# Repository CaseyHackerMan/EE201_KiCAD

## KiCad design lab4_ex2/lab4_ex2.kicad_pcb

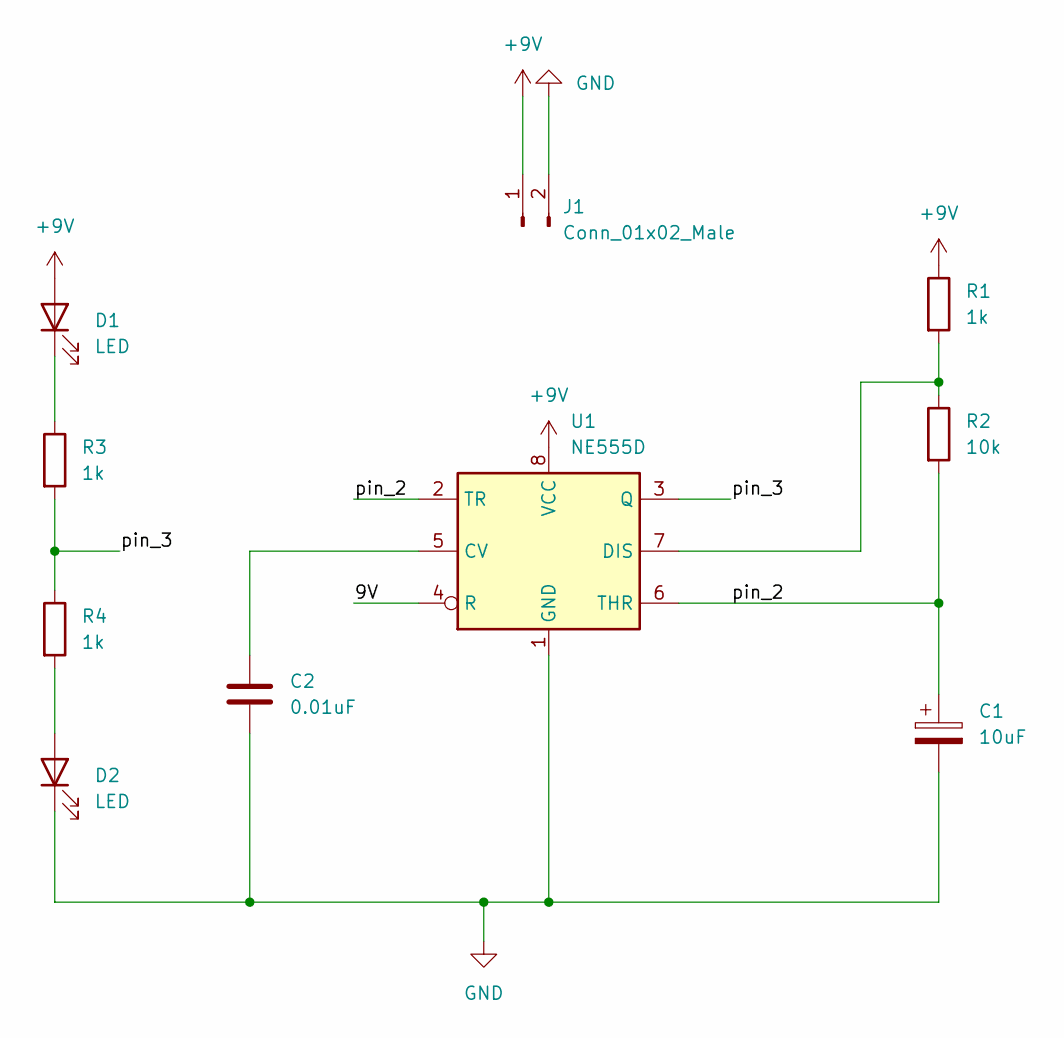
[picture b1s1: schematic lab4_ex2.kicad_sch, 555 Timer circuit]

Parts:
C1: 10uF; CP_EIA-3216-18_Kemet-A_Pad1.58x1.35mm_HandSolder
C2: 0.01uF; C_0805_2012Metric_Pad1.18x1.45mm_HandSolder
D1, D2: LED; LED_1206_3216Metric_Pad1.42x1.75mm_HandSolder
J1: Conn_01x02_Male; TerminalBlock_bornier-2_P5.08mm
R1, R3, R4: 1k; R_0805_2012Metric_Pad1.20x1.40mm_HandSolder
R2: 10k; R_0805_2012Metric_Pad1.20x1.40mm_HandSolder
U1: NE555D; SOIC-8-1EP_3.9x4.9mm_P1.27mm_EP2.29x3mm

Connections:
+9V: D1.2 (A), J1.1, R1.1, U1.8 (VCC)
/9V: U1.4 (R)
/pin_2: C1.1, R2.2, U1.2 (TR), U1.6 (THR), U1.9
/pin_3: R3.2, R4.1, U1.3 (Q)
GND: C1.2, C2.2, D2.1 (K), J1.2, U1.1 (GND)
unnamed: C2.1, U1.5 (CV)
unnamed: D1.1 (K), R3.1
unnamed: D2.2 (A), R4.2
unnamed: R1.2, R2.1, U1.7 (DIS)

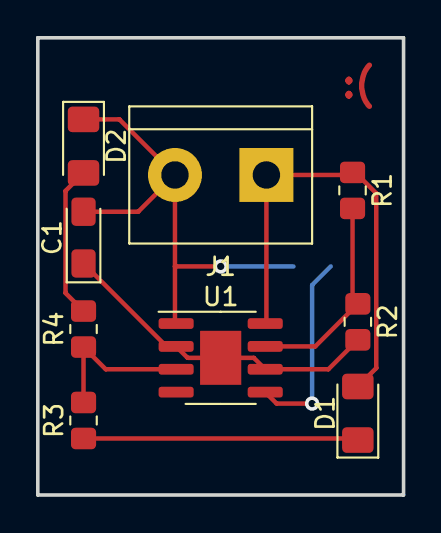
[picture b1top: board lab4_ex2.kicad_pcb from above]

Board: 2 copper layers, 20.3 x 25.4 mm, 10 parts (1 on the bottom side), 8 nets.

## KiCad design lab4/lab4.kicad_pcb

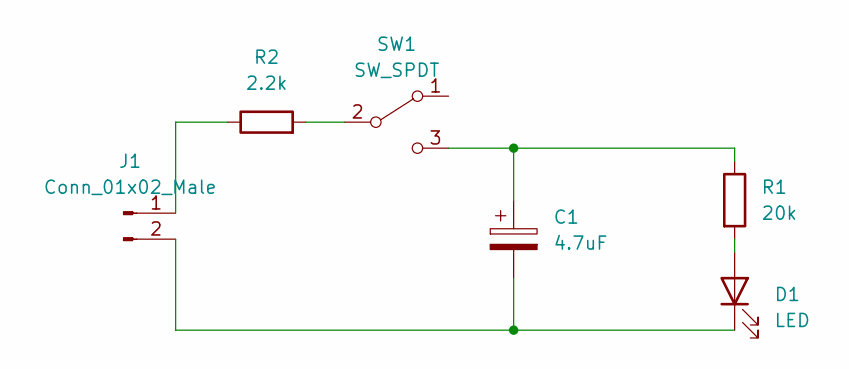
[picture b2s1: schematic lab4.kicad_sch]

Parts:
C1: 4.7uF; C_Radial_D5.0mm_H5.0mm_P2.00mm
D1: LED; LED_D5.0mm
J1: Conn_01x02_Male; JST_PH_B2B-PH-K_1x02_P2.00mm_Vertical
R1: 20k; R_Axial_DIN0516_L15.5mm_D5.0mm_P20.32mm_Horizontal
R2: 2.2k; R_Axial_DIN0516_L15.5mm_D5.0mm_P20.32mm_Horizontal
SW1: SW_SPDT; SW_E-Switch_EG1224_SPDT_Angled

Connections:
unnamed: C1.1, R1.1, SW1.3 (C)
unnamed: C1.2, D1.1 (K), J1.2
unnamed: D1.2 (A), R1.2
unnamed: J1.1, R2.1
unnamed: R2.2, SW1.2 (B)

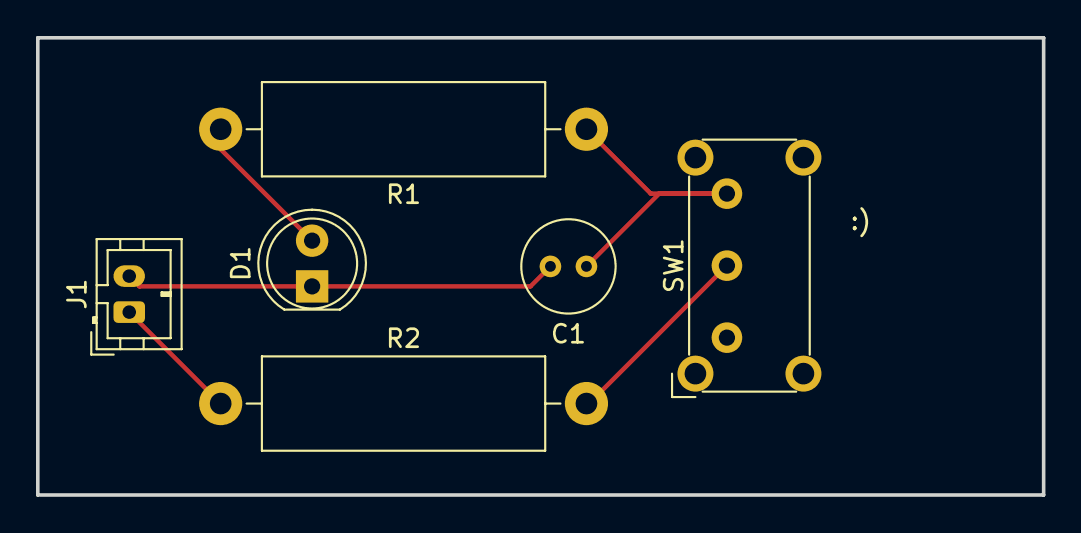
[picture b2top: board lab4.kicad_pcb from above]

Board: 2 copper layers, 55.9 x 25.4 mm, 6 parts (0 on the bottom side), 5 nets.

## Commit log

2023-01-26 title change
2023-02-09 Layout
2023-02-16 generated gerber/drill files
